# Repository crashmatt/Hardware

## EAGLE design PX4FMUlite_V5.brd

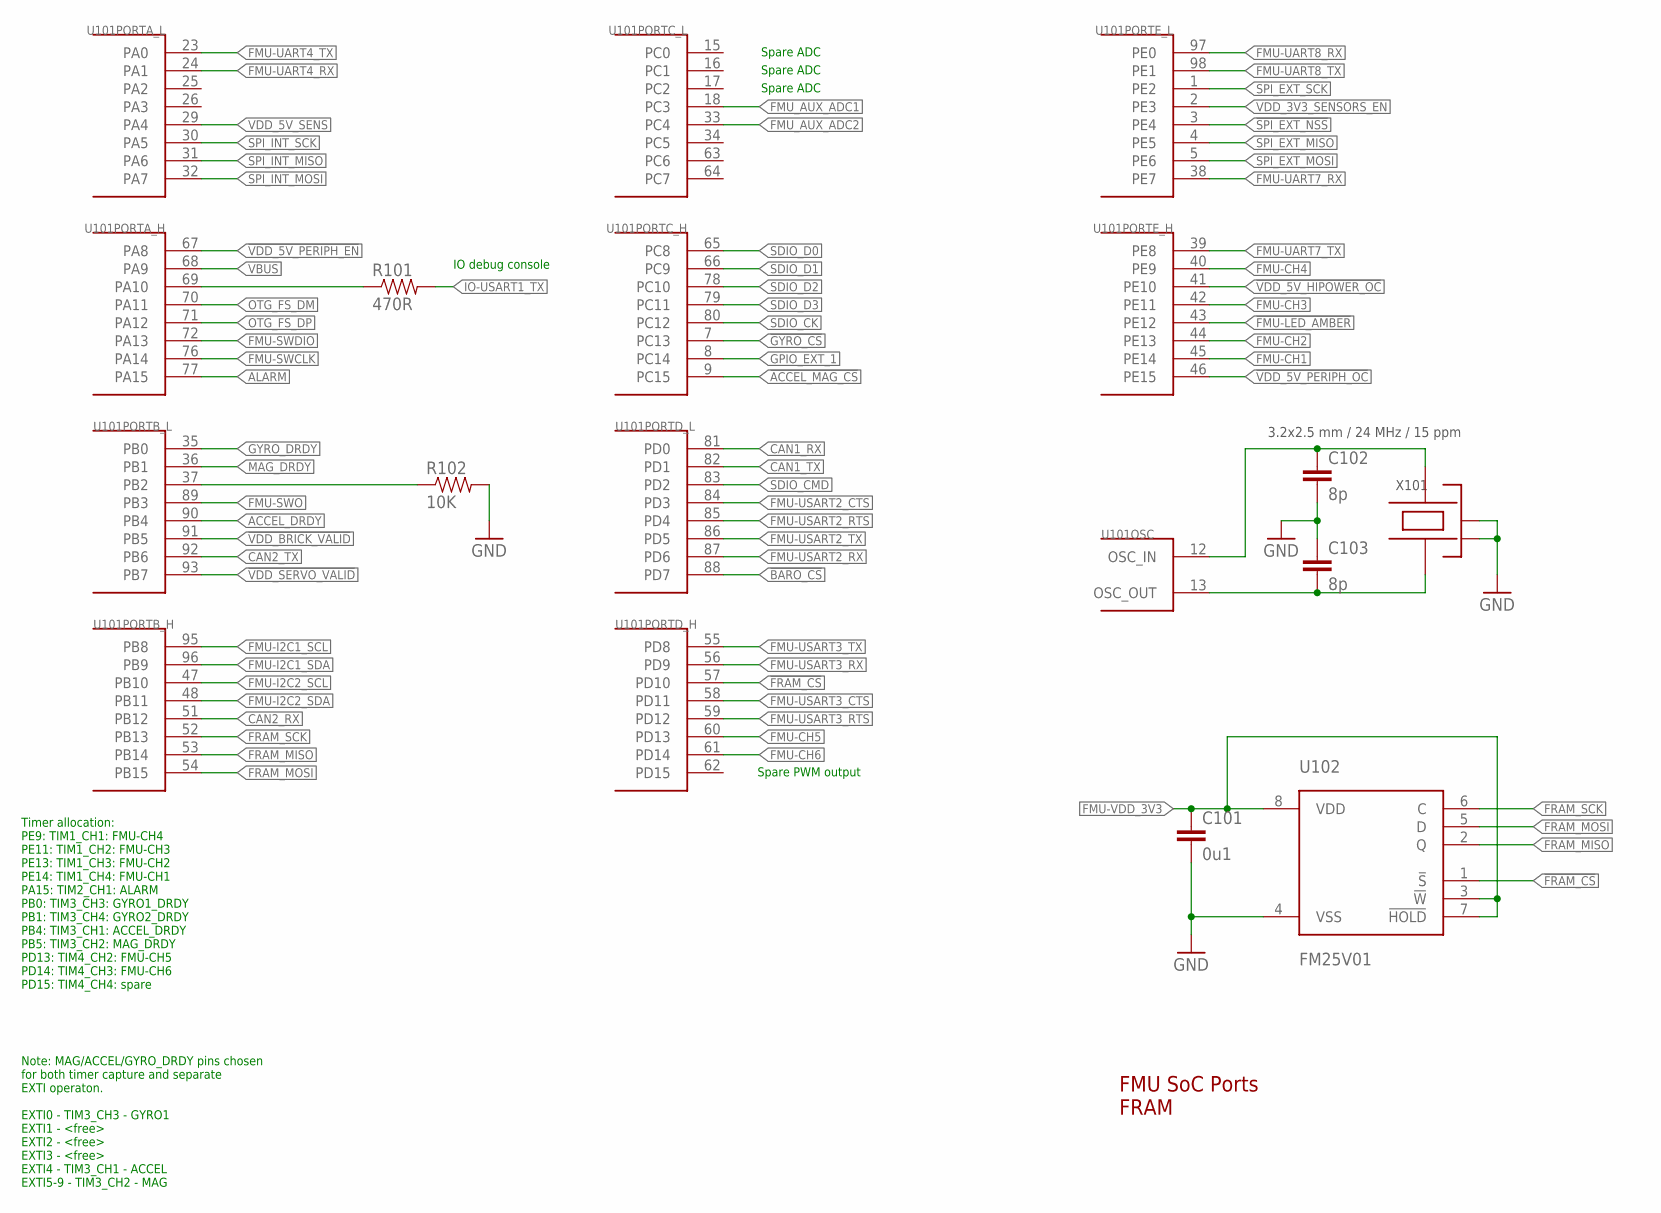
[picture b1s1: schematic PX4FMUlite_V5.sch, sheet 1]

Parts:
C101: 0u1; 0402-CAP; PARTNO CC0402ZRY5V7BB104
C102, C103: 8p; 0402-CAP; PARTNO C1005C0G1H080C
R101: 470R; 0402-RES; PARTNO RC0402FR-07470RL
R102: 10K; 0402-RES; PARTNO RC0402FR-0710KL
U101: STM32F4X7VX; TQFP100; PARTNO STM32F427VI
U102: FM25V01; SO08; PARTNO FM25V01-G
X101: 3.2x2.5 mm / 24 MHz / 15 ppm; OSCILLATOR-3.2X2.5; PARTNO NX3225SA-24.000000MHZ

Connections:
!ACCEL_MAG_CS: U101.9 (PC15); also elsewhere on the board
!BARO_CS: U101.88 (PD7); also elsewhere on the board
!FMU-LED_AMBER: U101.43 (PE12); also elsewhere on the board
!FRAM_CS: U101.57 (PD10), U102.1 (!S)
!GYRO_CS: U101.7 (PC13); also elsewhere on the board
!SPI_EXT_NSS: U101.3 (PE4); also elsewhere on the board
!VDD_5V_HIPOWER_OC: U101.41 (PE10)
!VDD_5V_PERIPH_EN: U101.67 (PA8); also elsewhere on the board
!VDD_5V_PERIPH_OC: U101.46 (PE15); also elsewhere on the board
!VDD_BRICK_VALID: U101.91 (PB5)
!VDD_SERVO_VALID: U101.93 (PB7)
ACCEL_DRDY: U101.90 (PB4); also elsewhere on the board
ALARM: U101.77 (PA15)
CAN1_RX: U101.81 (PD0); also elsewhere on the board
CAN1_TX: U101.82 (PD1); also elsewhere on the board
CAN2_RX: U101.51 (PB12); also elsewhere on the board
CAN2_TX: U101.92 (PB6); also elsewhere on the board
FMU-CH1: U101.45 (PE14); also elsewhere on the board
FMU-CH2: U101.44 (PE13); also elsewhere on the board
FMU-CH3: U101.42 (PE11); also elsewhere on the board
FMU-CH4: U101.40 (PE9); also elsewhere on the board
FMU-CH5: U101.60 (PD13); also elsewhere on the board
FMU-CH6: U101.61 (PD14); also elsewhere on the board
FMU-I2C1_SCL: U101.95 (PB8); also elsewhere on the board
FMU-I2C1_SDA: U101.96 (PB9); also elsewhere on the board
FMU-I2C2_SCL: U101.47 (PB10); also elsewhere on the board
FMU-I2C2_SDA: U101.48 (PB11); also elsewhere on the board
FMU-SWCLK: U101.76 (PA14); also elsewhere on the board
FMU-SWDIO: U101.72 (PA13); also elsewhere on the board
FMU-SWO: U101.89 (PB3); also elsewhere on the board
FMU-UART4_RX: U101.24 (PA1); also elsewhere on the board
FMU-UART4_TX: U101.23 (PA0); also elsewhere on the board
FMU-UART7_RX: U101.38 (PE7); also elsewhere on the board
FMU-UART7_TX: U101.39 (PE8); also elsewhere on the board
FMU-UART8_RX: U101.97 (PE0); also elsewhere on the board
FMU-UART8_TX: U101.98 (PE1); also elsewhere on the board
FMU-USART2_CTS: U101.84 (PD3); also elsewhere on the board
FMU-USART2_RTS: U101.85 (PD4); also elsewhere on the board
FMU-USART2_RX: U101.87 (PD6); also elsewhere on the board
FMU-USART2_TX: U101.86 (PD5); also elsewhere on the board
FMU-USART3_CTS: U101.58 (PD11); also elsewhere on the board
FMU-USART3_RTS: U101.59 (PD12); also elsewhere on the board
FMU-USART3_RX: U101.56 (PD9); also elsewhere on the board
FMU-USART3_TX: U101.55 (PD8); also elsewhere on the board
FMU-VDD_3V3: C101.P$1 (1), U102.3 (!W), U102.7 (!HOLD), U102.8 (VDD); also elsewhere on the board
FMU_AUX_ADC1: U101.18 (PC3); also elsewhere on the board
FMU_AUX_ADC2: U101.33 (PC4); also elsewhere on the board
FRAM_MISO: U101.53 (PB14), U102.2 (Q)
FRAM_MOSI: U101.54 (PB15), U102.5 (D)
FRAM_SCK: U101.52 (PB13), U102.6 (C)
GNDX: C101.P$2 (2), C102.P$2 (2), C103.P$1 (1), R102.P$2 (2), U102.4 (VSS), X101.2 (NC_2), X101.4 (NC_4); also elsewhere on the board
GPIO_EXT_1: U101.8 (PC14); also elsewhere on the board
GYRO_DRDY: U101.35 (PB0); also elsewhere on the board
IO-USART1_TX: R101.P$2 (2); also elsewhere on the board
MAG_DRDY: U101.36 (PB1); also elsewhere on the board
unnamed: C103.P$2 (2), U101.13 (OSC_OUT), X101.1
unnamed: C102.P$1 (1), U101.12 (OSC_IN), X101.3
unnamed: R101.P$1 (1), U101.69 (PA10)
OTG_FS_DM: U101.70 (PA11); also elsewhere on the board
OTG_FS_DP: U101.71 (PA12); also elsewhere on the board
PB2-BOOT1: R102.P$1 (1), U101.37 (PB2)
SDIO_CK: U101.80 (PC12); also elsewhere on the board
SDIO_CMD: U101.83 (PD2); also elsewhere on the board
SDIO_D0: U101.65 (PC8); also elsewhere on the board
SDIO_D1: U101.66 (PC9); also elsewhere on the board
SDIO_D2: U101.78 (PC10); also elsewhere on the board
SDIO_D3: U101.79 (PC11); also elsewhere on the board
SPI_EXT_MISO: U101.4 (PE5); also elsewhere on the board
SPI_EXT_MOSI: U101.5 (PE6); also elsewhere on the board
SPI_EXT_SCK: U101.1 (PE2); also elsewhere on the board
SPI_INT_MISO: U101.31 (PA6); also elsewhere on the board
SPI_INT_MOSI: U101.32 (PA7); also elsewhere on the board
SPI_INT_SCK: U101.30 (PA5); also elsewhere on the board
VBUS: U101.68 (PA9); also elsewhere on the board
VDD_3V3_SENSORS_EN: U101.2 (PE3); also elsewhere on the board
VDD_5V_SENS: U101.29 (PA4); also elsewhere on the board

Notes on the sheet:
FMU SoC Ports FRAM
Note: MAG/ACCEL/GYRO_DRDY pins chosen for both timer capture and separate EXTI operaton. EXTI0 - TIM3_CH3 - GYRO1 EXTI1 - <free> EXTI2 - <free> EXTI3 - <free> EXTI4 - TIM3_CH1 - ACCEL EXTI5-9 - TIM3_CH2 - MAG
Timer allocation: PE9: TIM1_CH1: FMU-CH4 PE11: TIM1_CH2: FMU-CH3 PE13: TIM1_CH3: FMU-CH2 PE14: TIM1_CH4: FMU-CH1 PA15: TIM2_CH1: ALARM PB0: TIM3_CH3: GYRO1_DRDY PB1: TIM3_CH4: GYRO2_DRDY PB4: TIM3_CH1: ACCEL_DRDY PB5: TIM3_CH2: MAG_DRDY PD13: TIM4_CH2: FMU-CH5 PD14: TIM4_CH3: FMU-CH6 PD15: TIM4_CH4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
Spare PWM output
IO debug console
Spare ADC

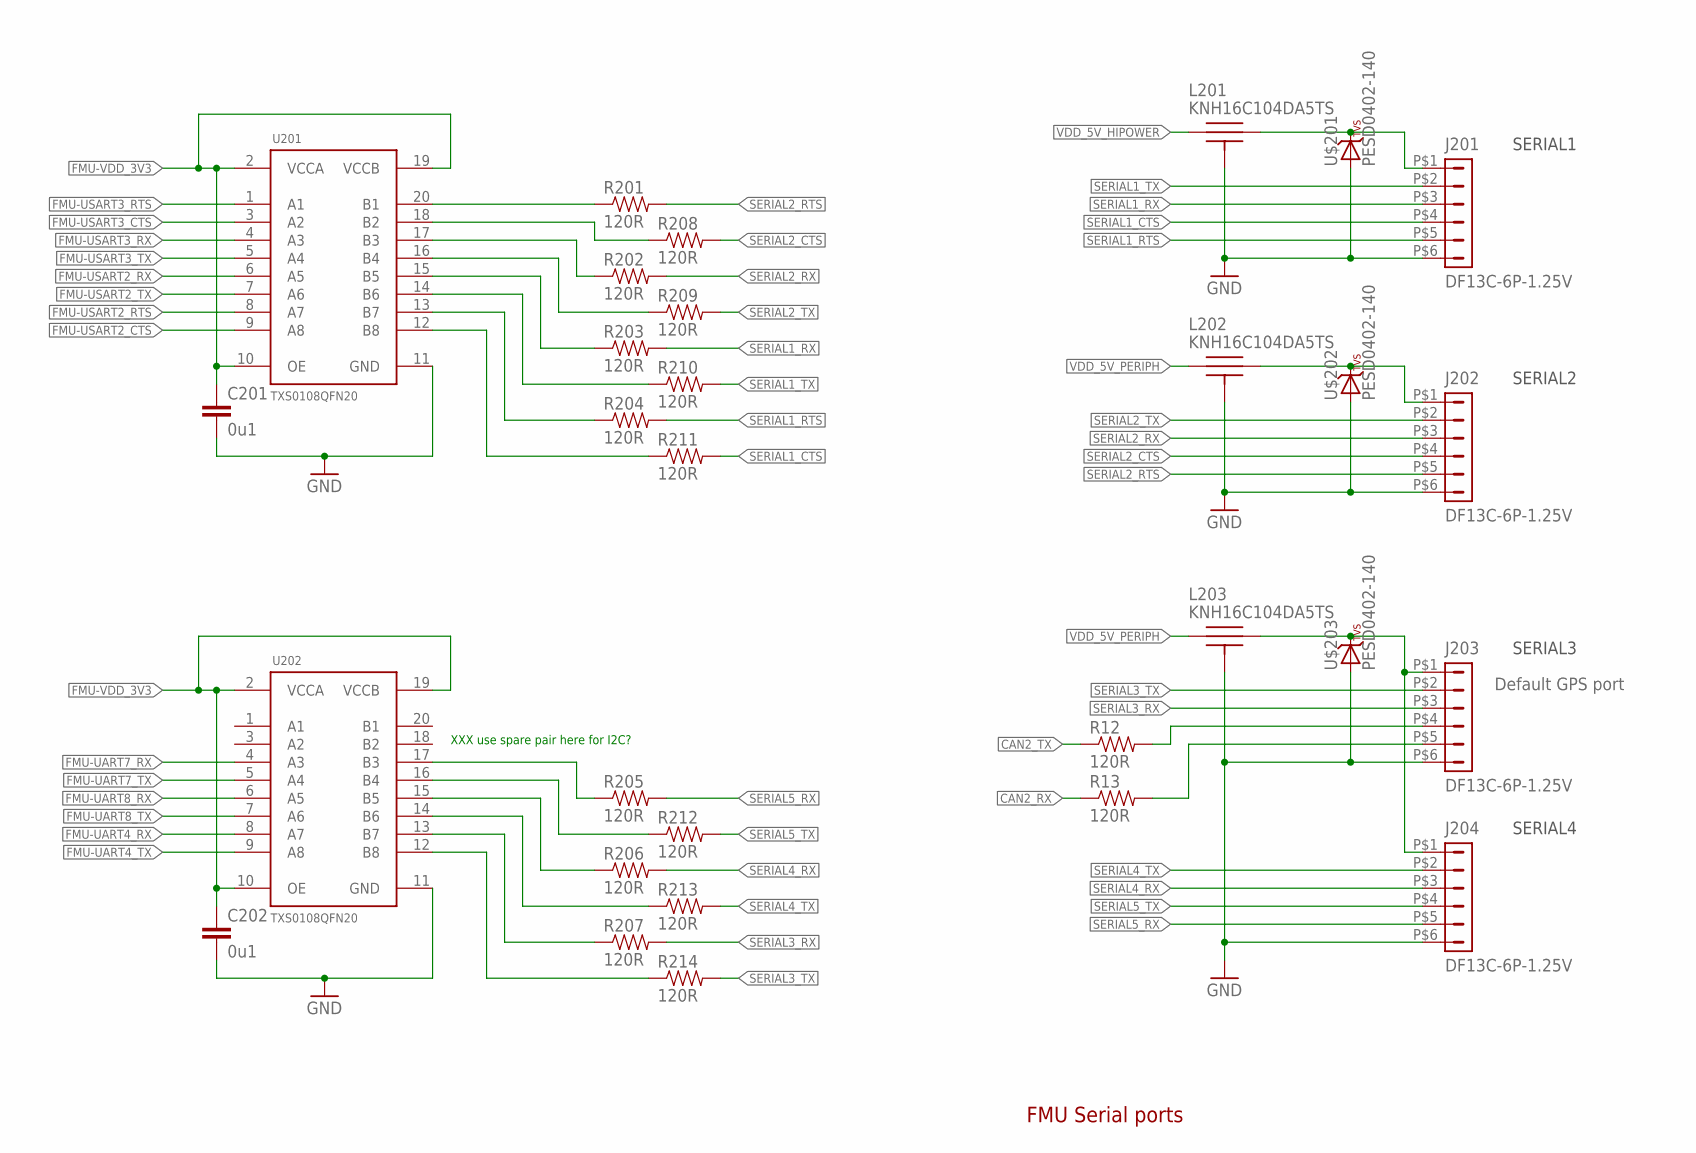
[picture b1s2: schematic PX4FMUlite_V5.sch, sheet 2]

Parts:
C201, C202: 0u1; 0402-CAP; PARTNO CC0402ZRY5V7BB104
J201, J202, J203, J204: DF13C-6P-1.25V; PARTNO DF13C-6P-1.25V(20)
L201, L202, L203: KNH16C104DA5TS; KYOCERA-KNH16-DA; PARTNO KNH16C104DA5TS
R12, R13, R201, R202, R203, R204, R205, R206, R207, R208, R209, R210, R211, R212, R213, R214: 120R; 0402-RES; PARTNO RC0402FR-07120RL
U201, U202: TXS0108QFN20; QFN20-RGY; PARTNO TXS0108ERGYR
U$201, U$202, U$203: PESD0402-140; 0402-TVS; PARTNO PESD0402-140

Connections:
CAN2_RX: R13.P$1 (1); also elsewhere on the board
CAN2_TX: R12.P$1 (1); also elsewhere on the board
FMU-UART4_RX: U202.8 (A7); also elsewhere on the board
FMU-UART4_TX: U202.9 (A8); also elsewhere on the board
FMU-UART7_RX: U202.4 (A3); also elsewhere on the board
FMU-UART7_TX: U202.5 (A4); also elsewhere on the board
FMU-UART8_RX: U202.6 (A5); also elsewhere on the board
FMU-UART8_TX: U202.7 (A6); also elsewhere on the board
FMU-USART2_CTS: U201.9 (A8); also elsewhere on the board
FMU-USART2_RTS: U201.8 (A7); also elsewhere on the board
FMU-USART2_RX: U201.6 (A5); also elsewhere on the board
FMU-USART2_TX: U201.7 (A6); also elsewhere on the board
FMU-USART3_CTS: U201.3 (A2); also elsewhere on the board
FMU-USART3_RTS: U201.1 (A1); also elsewhere on the board
FMU-USART3_RX: U201.4 (A3); also elsewhere on the board
FMU-USART3_TX: U201.5 (A4); also elsewhere on the board
FMU-VDD_3V3: C201.P$1 (1), C202.P$1 (1), U201.2 (VCCA), U201.10 (OE), U201.19 (VCCB), U202.2 (VCCA), U202.10 (OE), U202.19 (VCCB); also elsewhere on the board
GNDX: C201.P$2 (2), C202.P$2 (2), J201.P$6 (6), J202.P$6 (6), J203.P$6 (6), J204.P$6 (6), L201.P$3, L201.P$4, L201.P$5, L202.P$3, L202.P$4, L202.P$5, L203.P$3, L203.P$4, L203.P$5, U201.11 (GND), U202.11 (GND), U$201.A, U$202.A, U$203.A; also elsewhere on the board
unnamed: J201.P$1 (1), L201.P$2, U$201.C
unnamed: J203.P$4 (4), R12.P$2 (2)
unnamed: J203.P$5 (5), R13.P$2 (2)
unnamed: R201.P$1 (1), U201.20 (B1)
unnamed: R208.P$1 (1), U201.18 (B2)
unnamed: R202.P$1 (1), U201.17 (B3)
unnamed: R209.P$1 (1), U201.16 (B4)
unnamed: R203.P$1 (1), U201.15 (B5)
unnamed: R210.P$1 (1), U201.14 (B6)
unnamed: R204.P$1 (1), U201.13 (B7)
unnamed: R211.P$1 (1), U201.12 (B8)
unnamed: R207.P$1 (1), U202.13 (B7)
unnamed: R214.P$1 (1), U202.12 (B8)
unnamed: R205.P$1 (1), U202.17 (B3)
unnamed: R212.P$1 (1), U202.16 (B4)
unnamed: R206.P$1 (1), U202.15 (B5)
unnamed: R213.P$1 (1), U202.14 (B6)
unnamed: J203.P$1 (1), J204.P$1 (1), L203.P$2, U$203.C
unnamed: J202.P$1 (1), L202.P$2, U$202.C
SERIAL1_CTS: J201.P$4 (4), R211.P$2 (2)
SERIAL1_RTS: J201.P$5 (5), R204.P$2 (2)
SERIAL1_RX: J201.P$3 (3), R203.P$2 (2); also elsewhere on the board
SERIAL1_TX: J201.P$2 (2), R210.P$2 (2); also elsewhere on the board
SERIAL2_CTS: J202.P$4 (4), R208.P$2 (2)
SERIAL2_RTS: J202.P$5 (5), R201.P$2 (2)
SERIAL2_RX: J202.P$3 (3), R202.P$2 (2); also elsewhere on the board
SERIAL2_TX: J202.P$2 (2), R209.P$2 (2); also elsewhere on the board
SERIAL3_RX: J203.P$3 (3), R207.P$2 (2); also elsewhere on the board
SERIAL3_TX: J203.P$2 (2), R214.P$2 (2); also elsewhere on the board
SERIAL4_RX: J204.P$3 (3), R206.P$2 (2); also elsewhere on the board
SERIAL4_TX: J204.P$2 (2), R213.P$2 (2); also elsewhere on the board
SERIAL5_RX: J204.P$5 (5), R205.P$2 (2); also elsewhere on the board
SERIAL5_TX: J204.P$4 (4), R212.P$2 (2); also elsewhere on the board
VDD_5V_HIPOWER: L201.P$1
VDD_5V_PERIPH: L202.P$1, L203.P$1; also elsewhere on the board

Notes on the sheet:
FMU Serial ports
XXX use spare pair here for I2C?
SERIAL2
SERIAL1
SERIAL3
SERIAL4
Default GPS port

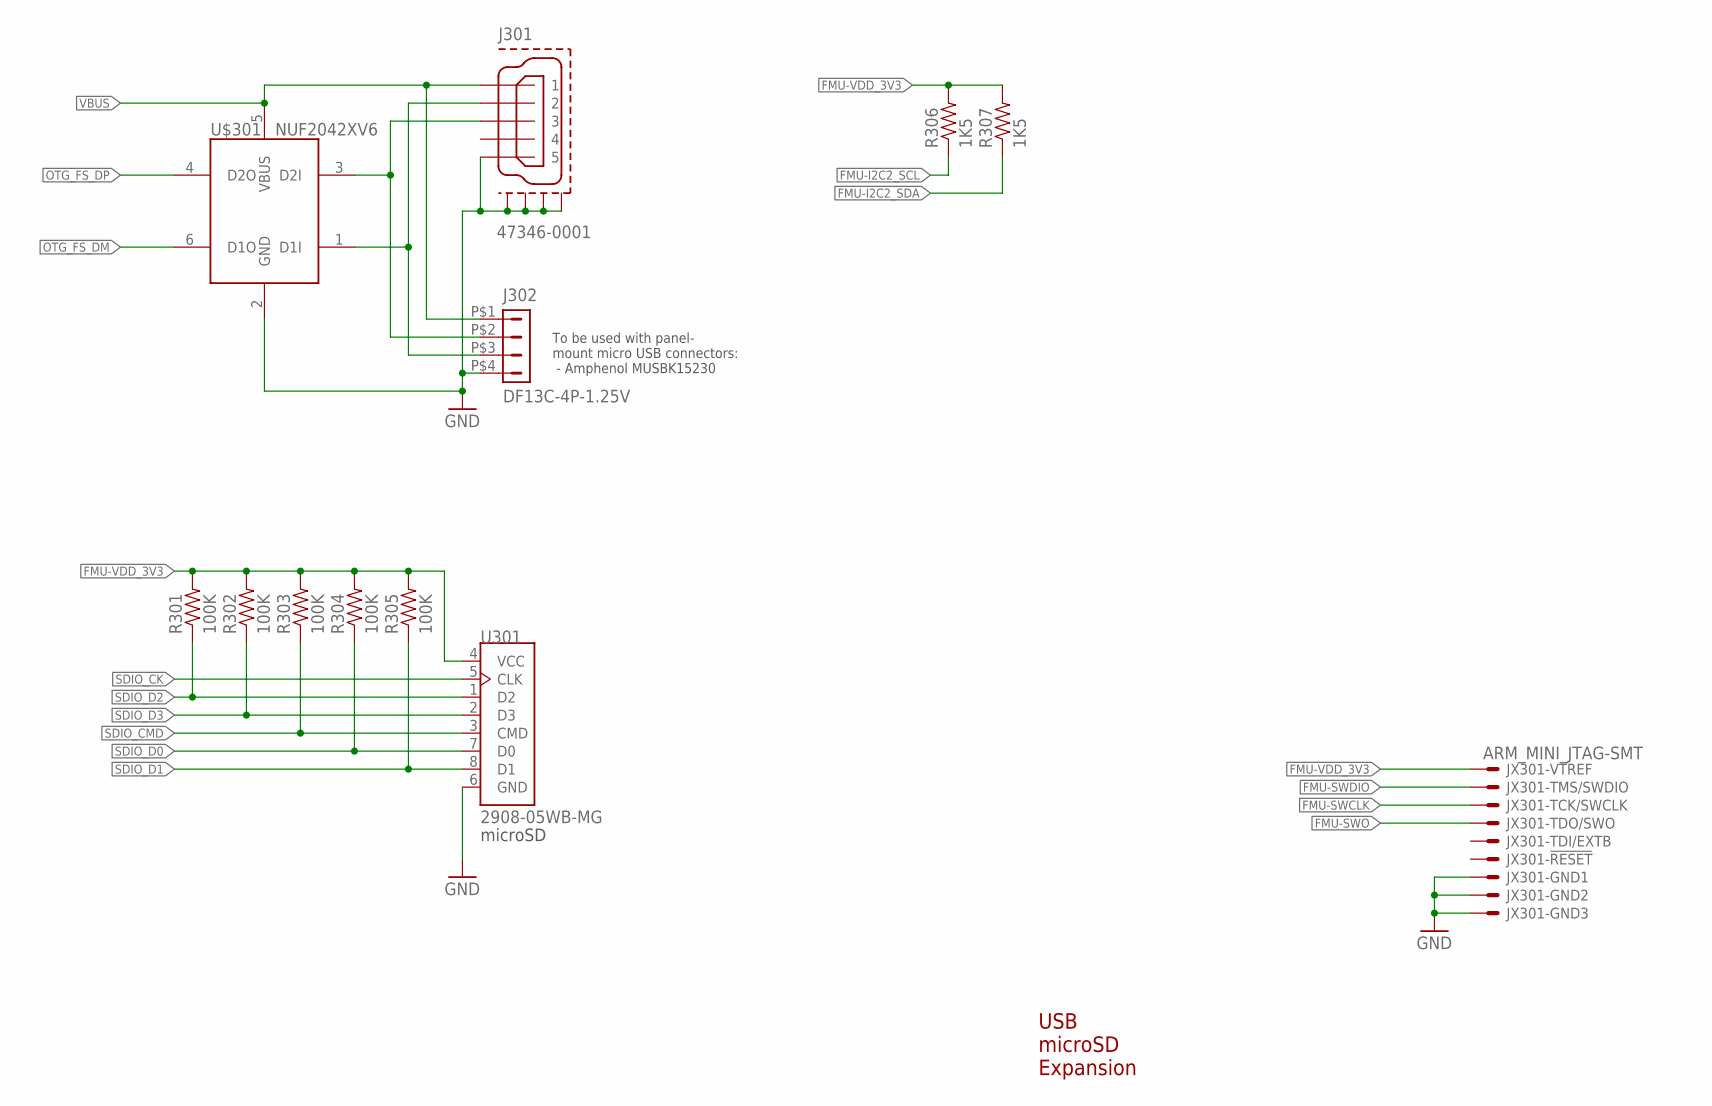
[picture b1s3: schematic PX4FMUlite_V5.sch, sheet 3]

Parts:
J301: 47346-0001; MOLEX-47346-0001; PARTNO 47346-0001
J302: DF13C-4P-1.25V; PARTNO DF13C-4P-1.25V(20)
JX301: ARM_MINI_JTAG-SMT; FTSH-105-01-XXX-DV-K; PARTNO M50-3900542
R301, R302, R303, R304, R305: 100K; 0402-RES; PARTNO RC0402FR-07100KL
R306, R307: 1K5; 0402-RES; PARTNO RC0402FR-071K5L
U301: 2908-05WB-MG; MICROSD; PARTNO 2908-05WB-MG
U$301: NUF2042XV6; SOT563-6; PARTNO NUF2042XV6T1G

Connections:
FMU-I2C2_SCL: R306.P$1 (1); also elsewhere on the board
FMU-I2C2_SDA: R307.P$1 (1); also elsewhere on the board
FMU-SWCLK: JX301.4; also elsewhere on the board
FMU-SWDIO: JX301.2; also elsewhere on the board
FMU-SWO: JX301.6; also elsewhere on the board
FMU-VDD_3V3: JX301.1, R301.P$2 (2), R302.P$2 (2), R303.P$2 (2), R304.P$2 (2), R305.P$2 (2), R306.P$2 (2), R307.P$2 (2), U301.4 (VCC); also elsewhere on the board
GNDX: J301.GND (5), J301.GND1, J301.GND2, J301.GND3, J301.GND4, J302.P$4 (4), JX301.3, JX301.5, JX301.9, U301.6 (GND), U$301.2 (GND); also elsewhere on the board
OTG_DM1: J301.D- (2), J302.P$3 (3), U$301.1 (D1I)
OTG_DP1: J301.D+ (3), J302.P$2 (2), U$301.3 (D2I)
OTG_FS_DM: U$301.6 (D1O); also elsewhere on the board
OTG_FS_DP: U$301.4 (D2O); also elsewhere on the board
SDIO_CK: U301.5 (CLK); also elsewhere on the board
SDIO_CMD: R303.P$1 (1), U301.3 (CMD); also elsewhere on the board
SDIO_D0: R304.P$1 (1), U301.7 (D0); also elsewhere on the board
SDIO_D1: R305.P$1 (1), U301.8 (D1); also elsewhere on the board
SDIO_D2: R301.P$1 (1), U301.1 (D2); also elsewhere on the board
SDIO_D3: R302.P$1 (1), U301.2 (D3); also elsewhere on the board
VBUS: J301.VBUS (1), J302.P$1 (1), U$301.5 (VBUS); also elsewhere on the board

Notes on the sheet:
USB microSD Expansion
microSD
To be used with panel- mount micro USB connectors: - Amphenol MUSBK15230

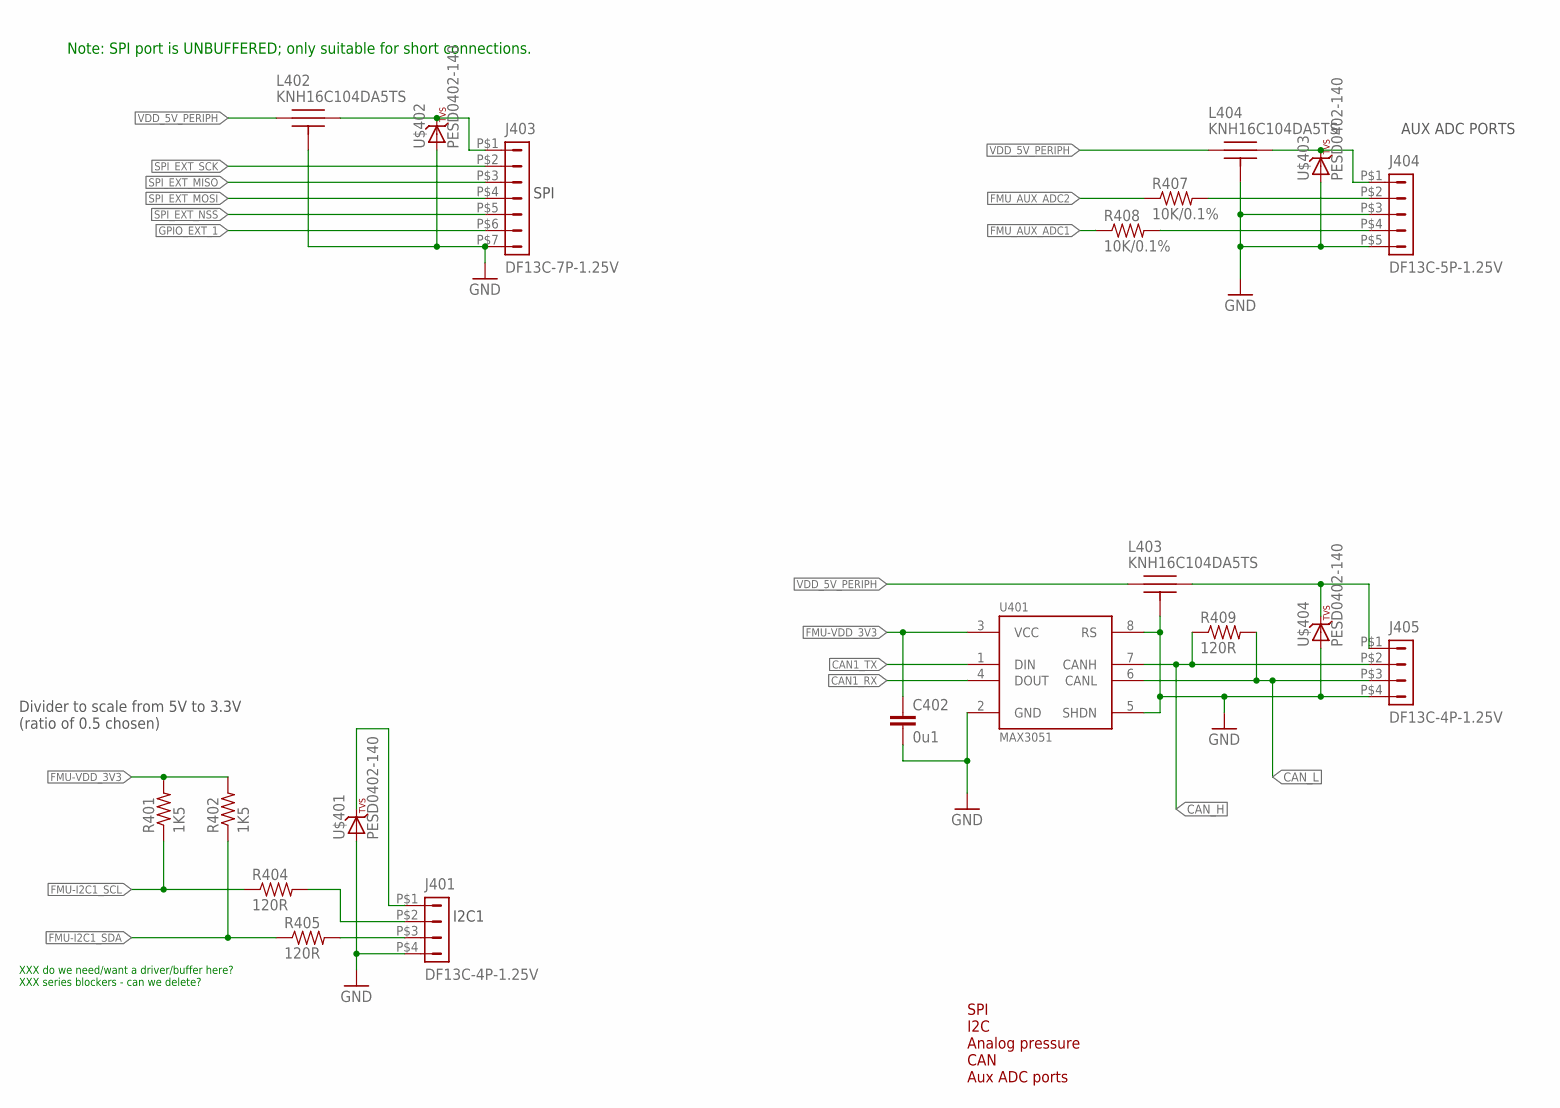
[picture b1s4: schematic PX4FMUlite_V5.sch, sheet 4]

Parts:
C402: 0u1; 0402-CAP; PARTNO CC0402ZRY5V7BB104
J401, J405: DF13C-4P-1.25V; PARTNO DF13C-4P-1.25V(20)
J403: DF13C-7P-1.25V; PARTNO DF13C-7P-1.25V(20)
J404: DF13C-5P-1.25V; PARTNO DF13C-5P-1.25V(20)
L402, L403, L404: KNH16C104DA5TS; KYOCERA-KNH16-DA; PARTNO KNH16C104DA5TS
R401, R402: 1K5; 0402-RES; PARTNO RC0402FR-071K5L
R404, R405, R409: 120R; 0402-RES; PARTNO RC0402FR-07120RL
R407, R408: 10K/0.1%; 0402-RES; PARTNO ERA-2AEB103X
U401: MAX3051; SOT23-8; PARTNO MAX3051EKA
U$401, U$402, U$403, U$404: PESD0402-140; 0402-TVS; PARTNO PESD0402-140

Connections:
!SPI_EXT_NSS: J403.P$5 (5); also elsewhere on the board
CAN1_RX: U401.4 (DOUT); also elsewhere on the board
CAN1_TX: U401.1 (DIN); also elsewhere on the board
CAN_H: J405.P$2 (2), R409.P$1 (1), U401.7 (CANH); also elsewhere on the board
CAN_L: J405.P$3 (3), R409.P$2 (2), U401.6 (CANL); also elsewhere on the board
FMU-I2C1_SCL: R401.P$1 (1), R404.P$1 (1); also elsewhere on the board
FMU-I2C1_SDA: R402.P$1 (1), R405.P$1 (1); also elsewhere on the board
FMU-VDD_3V3: C402.P$1 (1), R401.P$2 (2), R402.P$2 (2), U401.3 (VCC); also elsewhere on the board
FMU_AUX_ADC1: R408.P$1 (1); also elsewhere on the board
FMU_AUX_ADC1_PROT: J404.P$4 (4), R408.P$2 (2)
FMU_AUX_ADC2: R407.P$1 (1); also elsewhere on the board
FMU_AUX_ADC2_PROT: J404.P$2 (2), R407.P$2 (2)
GNDX: C402.P$2 (2), J401.P$4 (4), J403.P$7 (7), J404.P$3 (3), J404.P$5 (5), J405.P$4 (4), L402.P$3, L402.P$4, L402.P$5, L403.P$3, L403.P$4, L403.P$5, L404.P$3, L404.P$4, L404.P$5, U401.2 (GND), U401.5 (SHDN), U401.8 (RS), U$401.A, U$402.A, U$403.A, U$404.A; also elsewhere on the board
GPIO_EXT_1: J403.P$6 (6); also elsewhere on the board
unnamed: J401.P$2 (2), R404.P$2 (2)
unnamed: J401.P$3 (3), R405.P$2 (2)
unnamed: J403.P$1 (1), L402.P$2, U$402.C
unnamed: J401.P$1 (1), U$401.C
unnamed: J405.P$1 (1), L403.P$2, U$404.C
unnamed: J404.P$1 (1), L404.P$2, U$403.C
SPI_EXT_MISO: J403.P$3 (3); also elsewhere on the board
SPI_EXT_MOSI: J403.P$4 (4); also elsewhere on the board
SPI_EXT_SCK: J403.P$2 (2); also elsewhere on the board
VDD_5V_PERIPH: L402.P$1, L403.P$1, L404.P$1; also elsewhere on the board

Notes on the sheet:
SPI
XXX do we need/want a driver/buffer here? XXX series blockers - can we delete?
I2C1
AUX ADC PORTS
SPI I2C Analog pressure CAN Aux ADC ports
Note: SPI port is UNBUFFERED; only suitable for short connections.
Divider to scale from 5V to 3.3V (ratio of 0.5 chosen)

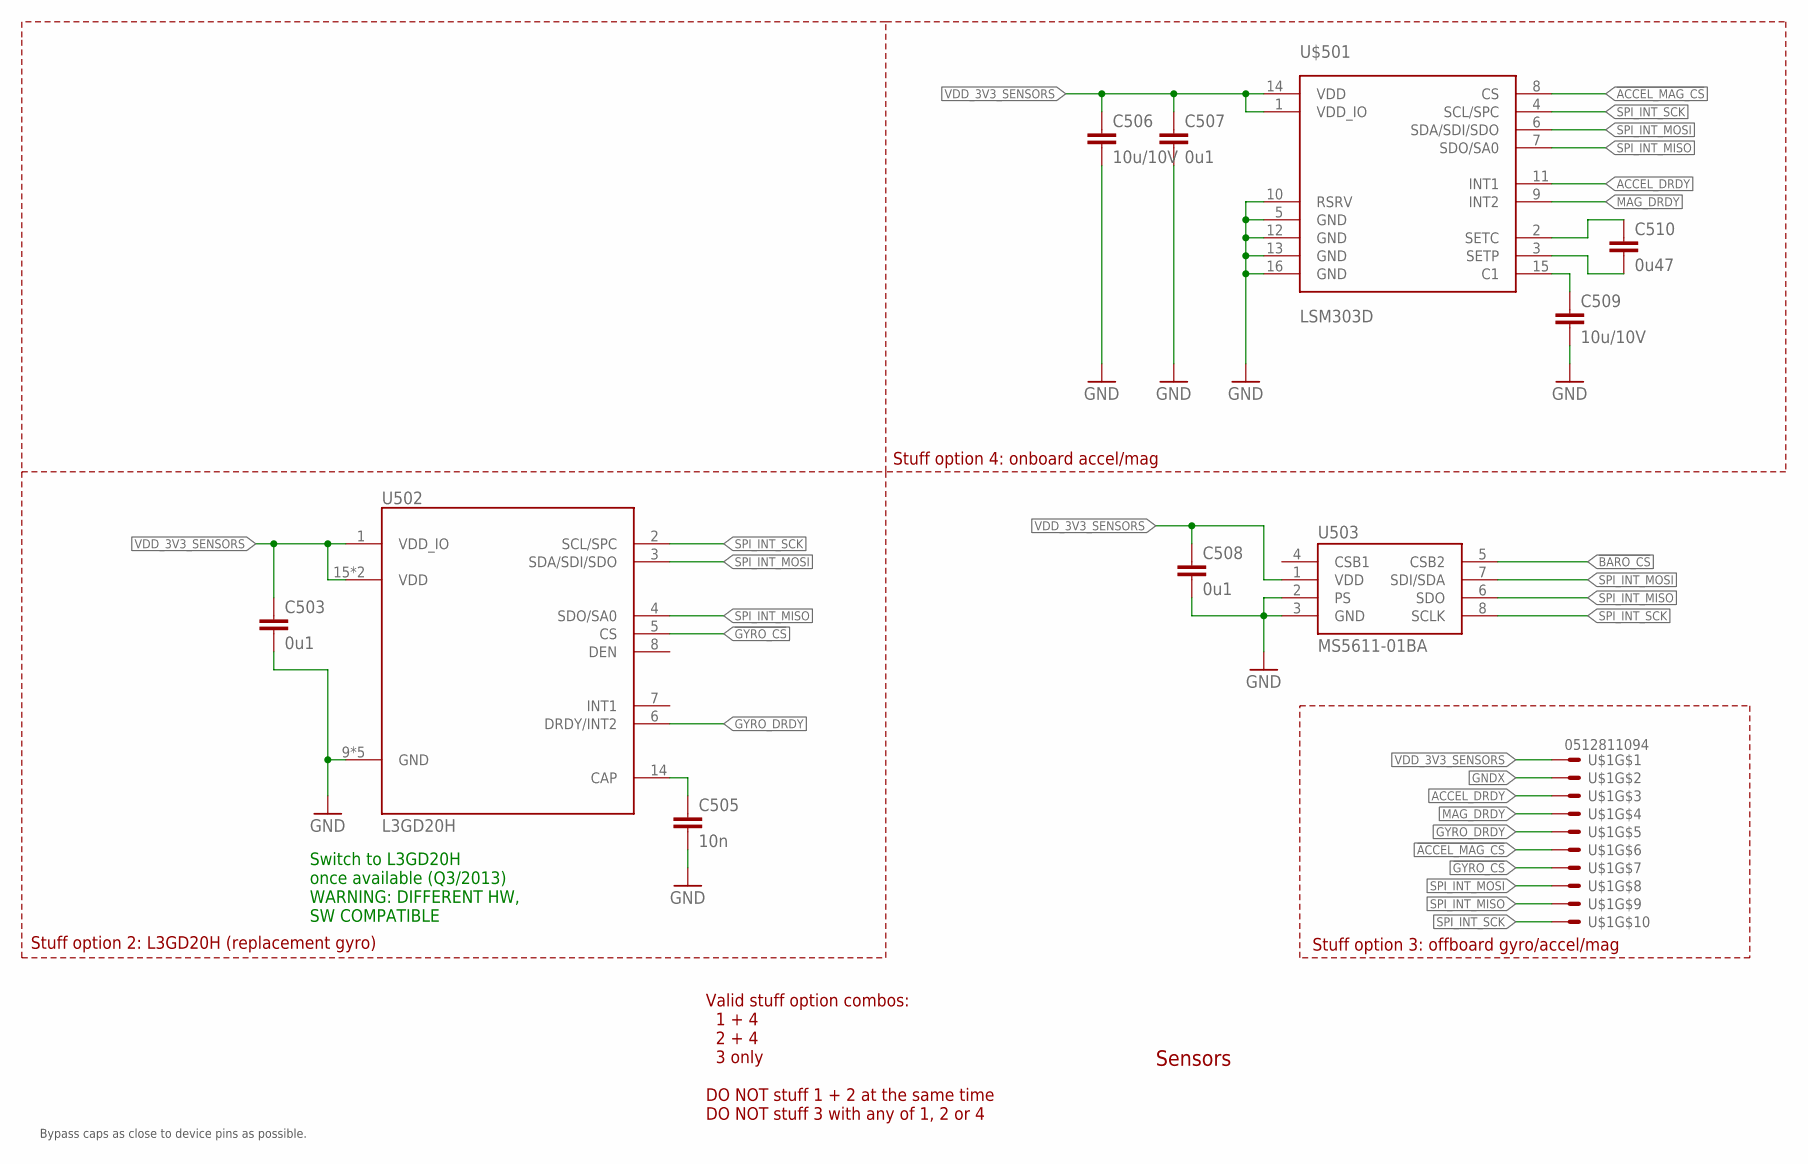
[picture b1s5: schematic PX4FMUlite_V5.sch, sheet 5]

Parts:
C503, C507, C508: 0u1; 0402-CAP; PARTNO CC0402ZRY5V7BB104
C505: 10n; 0402-CAP; PARTNO CC0402KRX7R7BB103
C506, C509: 10u/10V; 0805-CAP; PARTNO CC0805ZKY5V6BB106
C510: 0u47; 0402-CAP; PARTNO C1005X5R1C474K050BC
U502: L3GD20H; LGA-16L; PARTNO *
U503: MS5611-01BA; PARTNO MS5611-01BA
U$1: 0512811094; 51281-1094; PARTNO 0781191109
U$501: LSM303D; LGA-16L; PARTNO *

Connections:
!ACCEL_MAG_CS: U$1.6, U$501.8 (CS); also elsewhere on the board
!BARO_CS: U503.5 (CSB2); also elsewhere on the board
!GYRO_CS: U502.5 (CS), U$1.7; also elsewhere on the board
ACCEL_DRDY: U$1.3, U$501.11 (INT1); also elsewhere on the board
GNDX: C503.P$2 (2), C505.P$2 (2), C506.P$2 (2), C507.P$2 (2), C508.P$2 (2), C509.P$2 (2), U502.9 (GND), U502.10 (GND), U502.11 (GND), U502.12 (GND), U502.13 (GND), U503.2 (PS), U503.3 (GND), U$1.2, U$501.5 (GND), U$501.10 (RSRV), U$501.12 (GND), U$501.13 (GND), U$501.16 (GND); also elsewhere on the board
GYRO_DRDY: U502.6 (DRDY/INT2), U$1.5; also elsewhere on the board
MAG_DRDY: U$1.4, U$501.9 (INT2); also elsewhere on the board
unnamed: C509.P$1 (1), U$501.15 (C1)
unnamed: C510.P$1 (1), U$501.2 (SETC)
unnamed: C510.P$2 (2), U$501.3 (SETP)
unnamed: C505.P$1 (1), U502.14 (CAP)
SPI_INT_MISO: U502.4 (SDO/SA0), U503.6 (SDO), U$1.9, U$501.7 (SDO/SA0); also elsewhere on the board
SPI_INT_MOSI: U502.3 (SDA/SDI/SDO), U503.7 (SDI/SDA), U$1.8, U$501.6 (SDA/SDI/SDO); also elsewhere on the board
SPI_INT_SCK: U502.2 (SCL/SPC), U503.8 (SCLK), U$1.10, U$501.4 (SCL/SPC); also elsewhere on the board
VDD_3V3_SENSORS: C503.P$1 (1), C506.P$1 (1), C507.P$1 (1), C508.P$1 (1), U502.1 (VDD_IO), U502.15 (VDD), U502.16 (VDD), U503.1 (VDD), U$1.1, U$501.1 (VDD_IO), U$501.14 (VDD); also elsewhere on the board

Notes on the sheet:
Sensors
Bypass caps as close to device pins as possible.
Switch to L3GD20H once available (Q3/2013) WARNING: DIFFERENT HW, SW COMPATIBLE
Stuff option 2: L3GD20H (replacement gyro)
Stuff option 3: offboard gyro/accel/mag
Stuff option 4: onboard accel/mag
Valid stuff option combos: 1 + 4 2 + 4 3 only DO NOT stuff 1 + 2 at the same time DO NOT stuff 3 with any of 1, 2 or 4

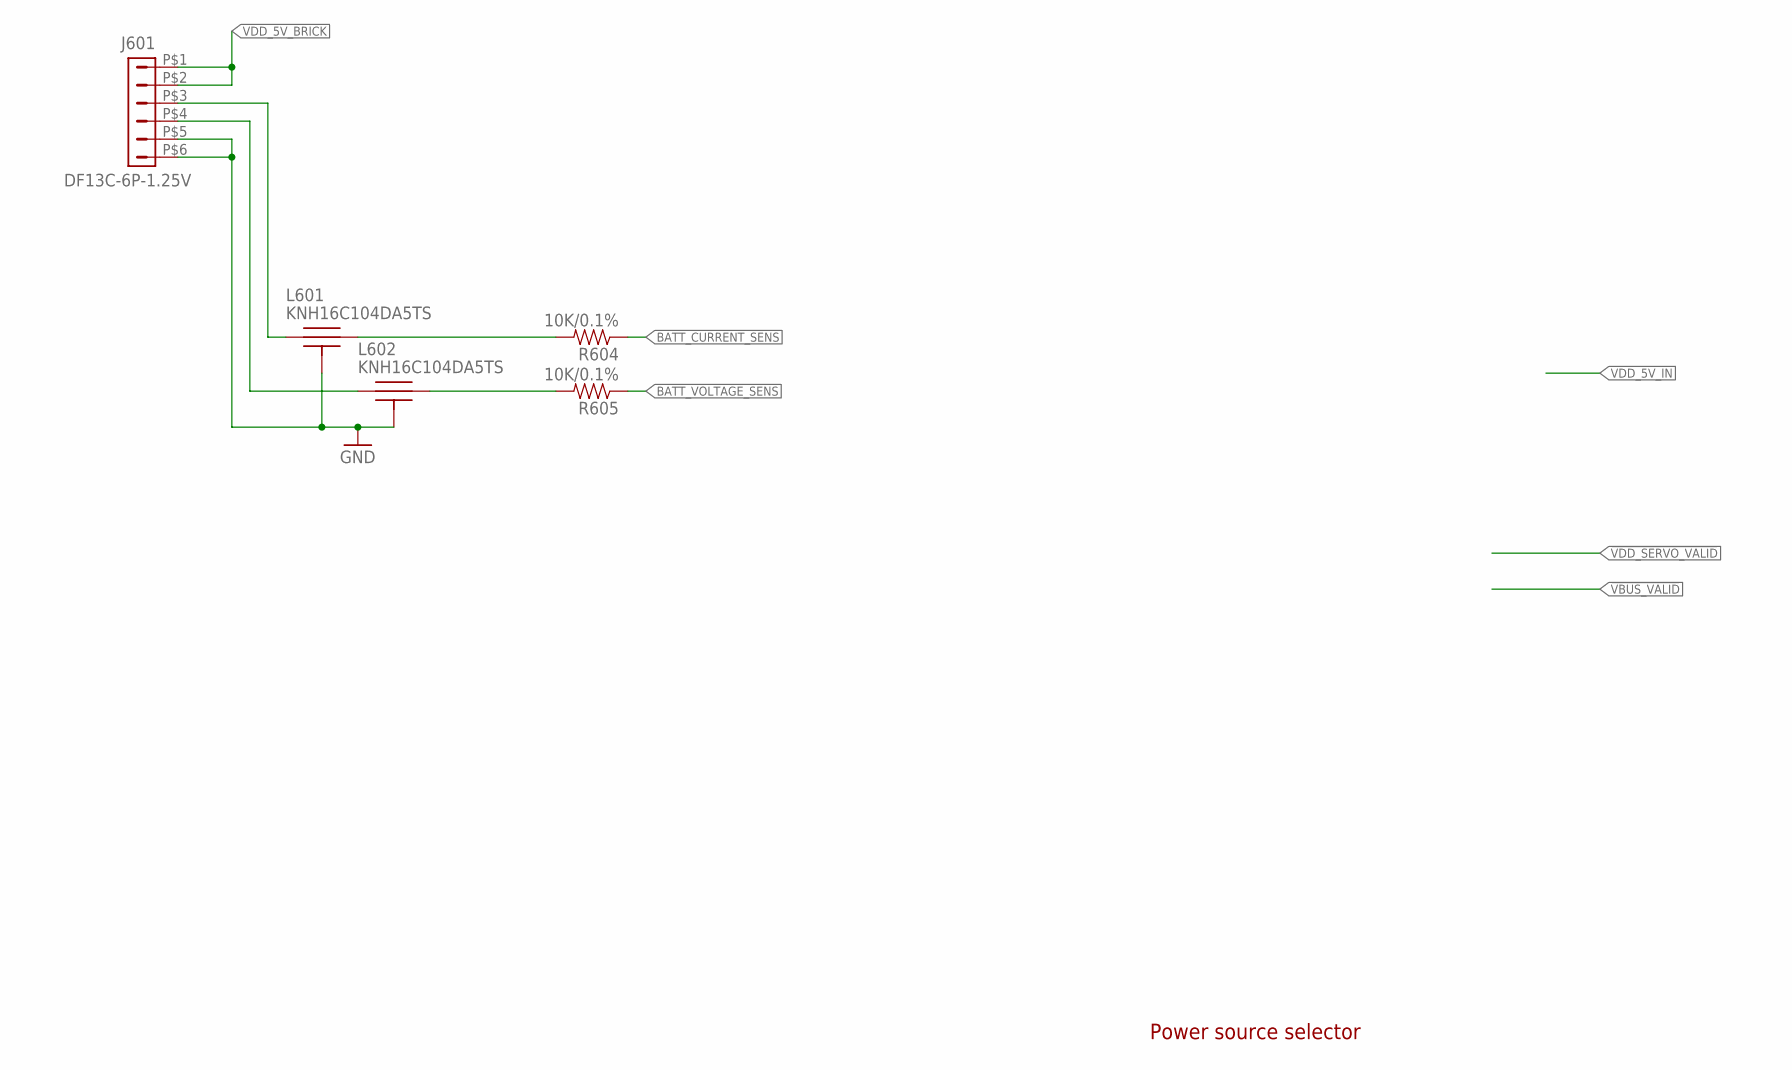
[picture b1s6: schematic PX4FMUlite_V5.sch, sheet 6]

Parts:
J601: DF13C-6P-1.25V; PARTNO DF13C-6P-1.25V(20)
L601, L602: KNH16C104DA5TS; KYOCERA-KNH16-DA; PARTNO KNH16C104DA5TS
R604, R605: 10K/0.1%; 0402-RES; PARTNO ERA-2AEB103X

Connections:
BATT_CURRENT_SENS: R604.P$1 (1)
BATT_CURRENT_SENS_PROT: J601.P$3 (3), L601.P$1
BATT_VOLTAGE_SENS: R605.P$1 (1)
BATT_VOLTAGE_SENS_PROT: J601.P$4 (4), L602.P$1
GNDX: J601.P$5 (5), J601.P$6 (6), L601.P$3, L601.P$4, L601.P$5, L602.P$3, L602.P$4, L602.P$5; also elsewhere on the board
unnamed: L602.P$2, R605.P$2 (2)
unnamed: L601.P$2, R604.P$2 (2)
VDD_5V_BRICK: J601.P$1 (1), J601.P$2 (2); also elsewhere on the board

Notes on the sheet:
Power source selector

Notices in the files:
PX4FMUlite_V5.brd:
(c) 2013 mjs/lm/jo
